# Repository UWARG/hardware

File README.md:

# Waterloo Aerial Robotics Group Hardware Repository

## Information
This repository previously held WARG electricals designs (Altium Schematics, PCBs, & Libraries) from roughly 2021 to 2022. In mid 2022 we switched solely toward Altium 365, https://warg.365.altium.com/ , and have largely abandonned this repository. Ideally we would upload completed projects to this Github for safe keeping in case anything happens with our Altium 365. 
For further documentation see Confluence, https://uwarg-docs.atlassian.net/wiki/spaces/EL/overview , or our team Discord.

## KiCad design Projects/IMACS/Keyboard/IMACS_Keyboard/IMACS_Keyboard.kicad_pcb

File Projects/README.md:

# Water System Controller

Confluence Information: https://uwarg-docs.atlassian.net/wiki/spaces/EL/pages/2765914176/Water+System+Controller

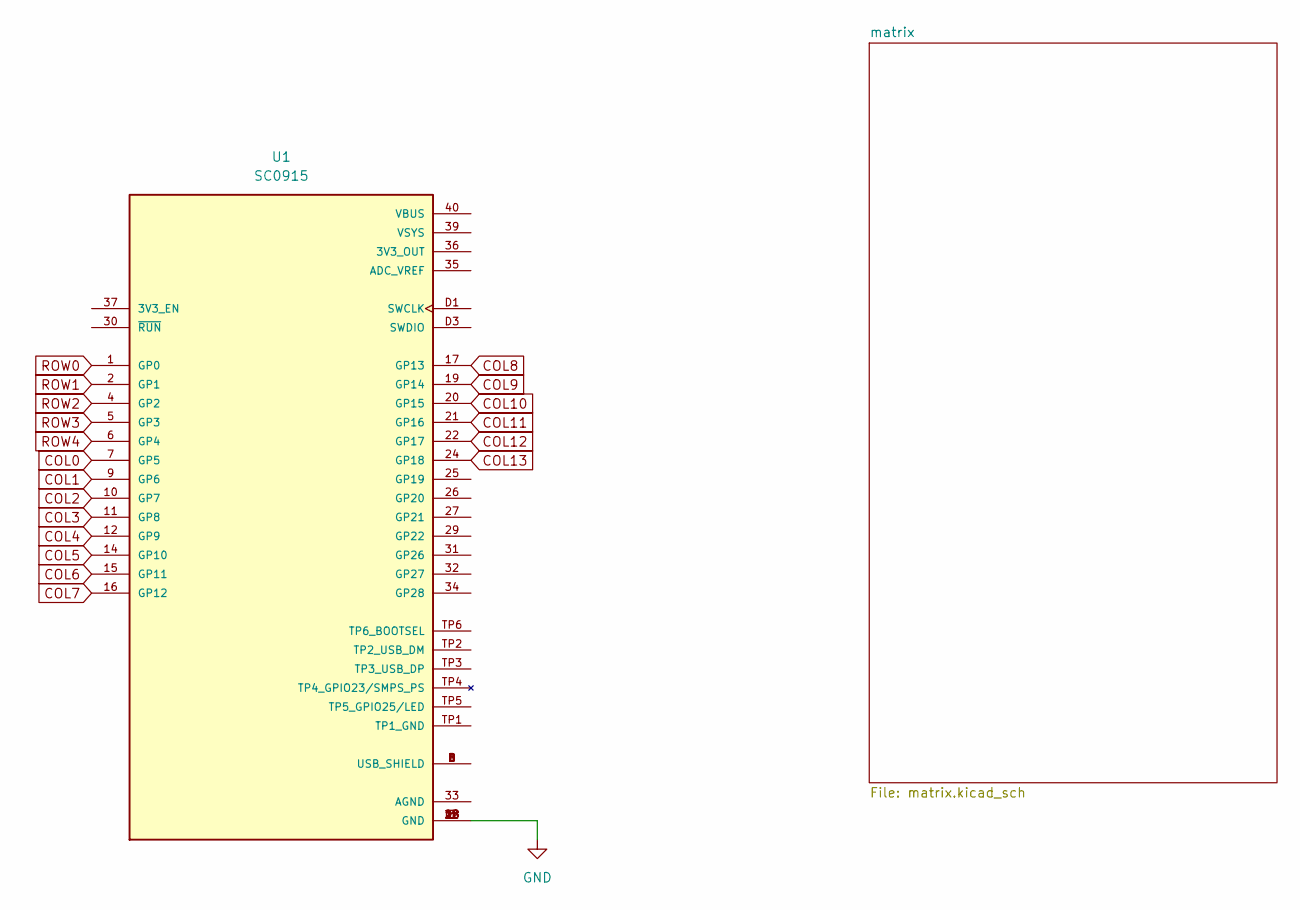
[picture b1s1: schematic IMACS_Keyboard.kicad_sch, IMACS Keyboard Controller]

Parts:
U1: SC0915; MODULE_SC0915; PARTREV 1.9

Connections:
COL0: U1.7 (GP5); also elsewhere on the board
COL1: U1.9 (GP6); also elsewhere on the board
COL2: U1.10 (GP7); also elsewhere on the board
COL3: U1.11 (GP8); also elsewhere on the board
COL4: U1.12 (GP9); also elsewhere on the board
COL5: U1.14 (GP10); also elsewhere on the board
COL6: U1.15 (GP11); also elsewhere on the board
COL7: U1.16 (GP12); also elsewhere on the board
COL8: U1.17 (GP13); also elsewhere on the board
COL9: U1.19 (GP14); also elsewhere on the board
COL10: U1.20 (GP15); also elsewhere on the board
COL11: U1.21 (GP16); also elsewhere on the board
COL12: U1.22 (GP17); also elsewhere on the board
COL13: U1.24 (GP18); also elsewhere on the board
GND: U1.3 (GND), U1.8 (GND), U1.13 (GND), U1.18 (GND), U1.23 (GND), U1.28 (GND), U1.38 (GND), U1.D2 (GND)
unnamed: U1.A (USB_SHIELD), U1.B (USB_SHIELD), U1.C (USB_SHIELD), U1.D (USB_SHIELD)
ROW0: U1.1 (GP0); also elsewhere on the board
ROW1: U1.2 (GP1); also elsewhere on the board
ROW2: U1.4 (GP2); also elsewhere on the board
ROW3: U1.5 (GP3); also elsewhere on the board
ROW4: U1.6 (GP4); also elsewhere on the board

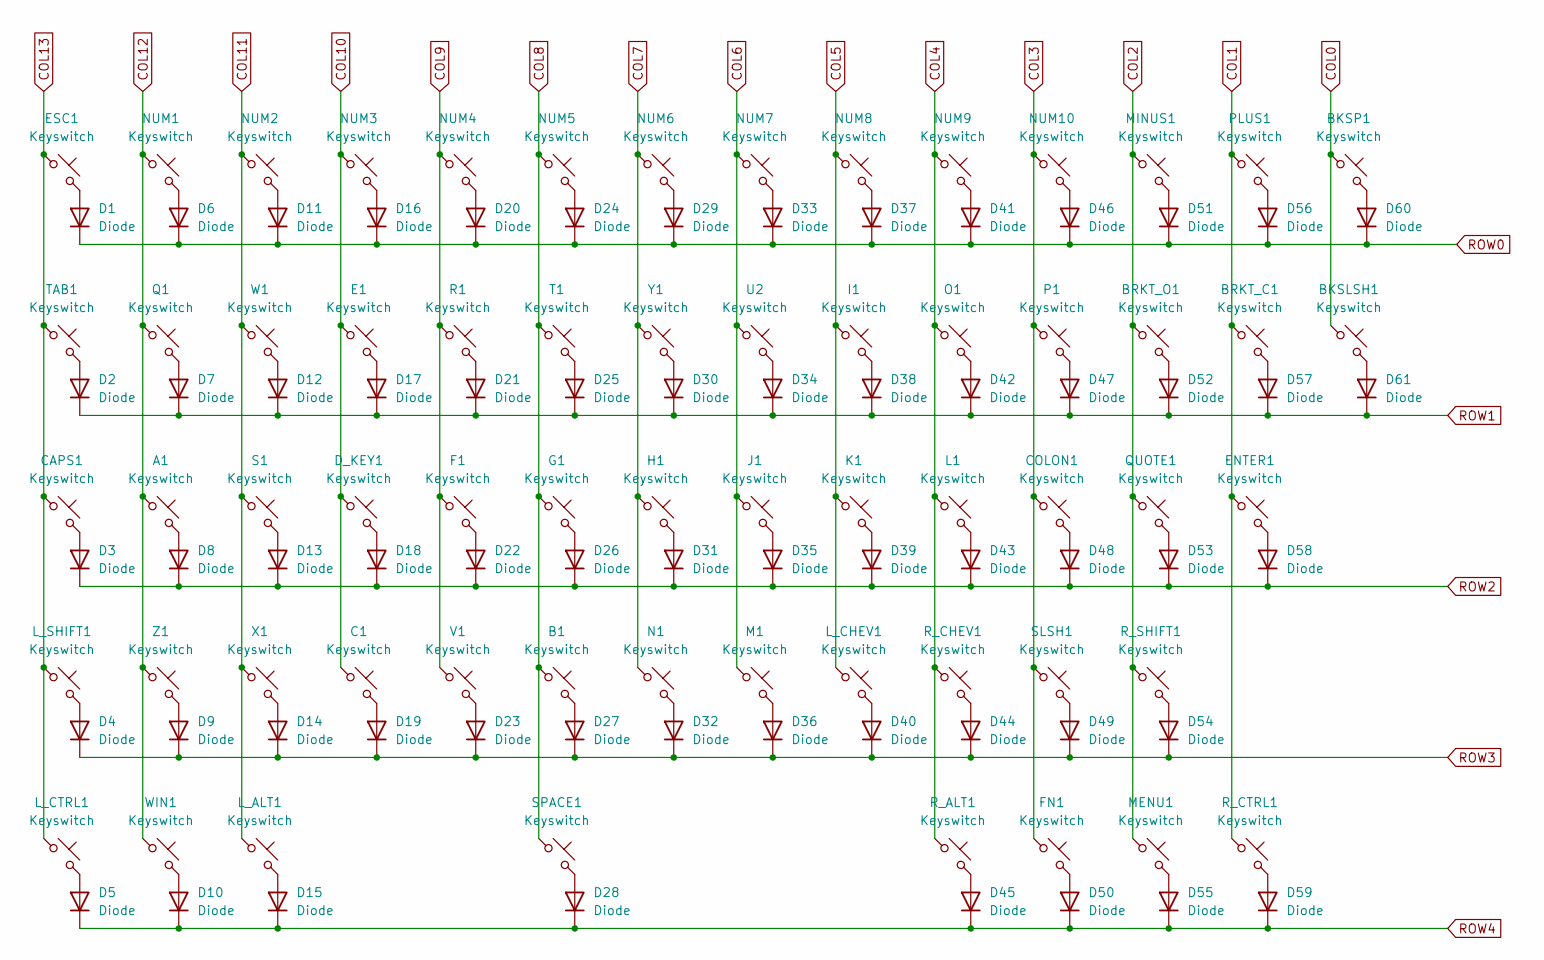
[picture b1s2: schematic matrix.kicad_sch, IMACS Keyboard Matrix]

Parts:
A1: Keyswitch; MX_PCB_1.00u
B1: Keyswitch; MX_PCB_1.00u
BKSLSH1: Keyswitch; MX_PCB_1.00u
BKSP1: Keyswitch; MX_PCB_1.00u
BRKT_C1: Keyswitch; MX_PCB_1.00u
BRKT_O1: Keyswitch; MX_PCB_1.00u
C1: Keyswitch; MX_PCB_1.00u
CAPS1: Keyswitch; MX_PCB_1.00u
COLON1: Keyswitch; MX_PCB_1.00u
D1, D2, D3, D4, D5, D6, D7, D8, D9, D10, D11, D12, D13, D14, D15, D16, D17, D18, D19, D20, D21, D22, D23, D24, D25, D26, D27, D28, D29, D30, D31, D32, D33, D34, D35, D36, D37, D38, D39, D40, D41, D42, D43, D44, D45, D46, D47, D48, D49, D50, D51, D52, D53, D54, D55, D56, D57, D58, D59, D60, D61: Diode; Diode_DO-35
D_KEY1: Keyswitch; MX_PCB_1.00u
E1: Keyswitch; MX_PCB_1.00u
ENTER1: Keyswitch; MX_PCB_1.00u
ESC1: Keyswitch; MX_PCB_1.00u
F1: Keyswitch; MX_PCB_1.00u
FN1: Keyswitch; MX_PCB_1.00u
G1: Keyswitch; MX_PCB_1.00u
H1: Keyswitch; MX_PCB_1.00u
I1: Keyswitch; MX_PCB_1.00u
J1: Keyswitch; MX_PCB_1.00u
K1: Keyswitch; MX_PCB_1.00u
L1: Keyswitch; MX_PCB_1.00u
L_ALT1: Keyswitch; MX_PCB_1.00u
L_CHEV1: Keyswitch; MX_PCB_1.00u
L_CTRL1: Keyswitch; MX_PCB_1.00u
L_SHIFT1: Keyswitch; MX_PCB_1.00u
M1: Keyswitch; MX_PCB_1.00u
MENU1: Keyswitch; MX_PCB_1.00u
MINUS1: Keyswitch; MX_PCB_1.00u
N1: Keyswitch; MX_PCB_1.00u
NUM1, NUM2, NUM3, NUM4, NUM5, NUM6, NUM7, NUM8, NUM9, NUM10: Keyswitch; MX_PCB_1.00u
O1: Keyswitch; MX_PCB_1.00u
P1: Keyswitch; MX_PCB_1.00u
PLUS1: Keyswitch; MX_PCB_1.00u
Q1: Keyswitch; MX_PCB_1.00u
QUOTE1: Keyswitch; MX_PCB_1.00u
R1: Keyswitch; MX_PCB_1.00u
R_ALT1: Keyswitch; MX_PCB_1.00u
R_CHEV1: Keyswitch; MX_PCB_1.00u
R_CTRL1: Keyswitch; MX_PCB_1.00u
R_SHIFT1: Keyswitch; MX_PCB_1.00u
S1: Keyswitch; MX_PCB_1.00u
SLSH1: Keyswitch; MX_PCB_1.00u
SPACE1: Keyswitch; MX_PCB_1.00u
T1: Keyswitch; MX_PCB_1.00u
TAB1: Keyswitch; MX_PCB_1.00u
U2: Keyswitch; MX_PCB_1.00u
V1: Keyswitch; MX_PCB_1.00u
W1: Keyswitch; MX_PCB_1.00u
WIN1: Keyswitch; MX_PCB_1.00u
X1: Keyswitch; MX_PCB_1.00u
Y1: Keyswitch; MX_PCB_1.00u
Z1: Keyswitch; MX_PCB_1.00u

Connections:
COL0: BKSLSH1.1, BKSP1.1; also elsewhere on the board
COL1: BRKT_C1.1, ENTER1.1, PLUS1.1, R_CTRL1.1; also elsewhere on the board
COL2: BRKT_O1.1, MENU1.1, MINUS1.1, QUOTE1.1, R_SHIFT1.1; also elsewhere on the board
COL3: COLON1.1, FN1.1, NUM10.1, P1.1, SLSH1.1; also elsewhere on the board
COL4: L1.1, NUM9.1, O1.1, R_ALT1.1, R_CHEV1.1; also elsewhere on the board
COL5: I1.1, K1.1, L_CHEV1.1, NUM8.1; also elsewhere on the board
COL6: J1.1, M1.1, NUM7.1, U2.1; also elsewhere on the board
COL7: H1.1, N1.1, NUM6.1, Y1.1; also elsewhere on the board
COL8: B1.1, G1.1, NUM5.1, SPACE1.1, T1.1; also elsewhere on the board
COL9: F1.1, NUM4.1, R1.1, V1.1; also elsewhere on the board
COL10: C1.1, D_KEY1.1, E1.1, NUM3.1; also elsewhere on the board
COL11: L_ALT1.1, NUM2.1, S1.1, W1.1, X1.1; also elsewhere on the board
COL12: A1.1, NUM1.1, Q1.1, WIN1.1, Z1.1; also elsewhere on the board
COL13: CAPS1.1, ESC1.1, L_CTRL1.1, L_SHIFT1.1, TAB1.1; also elsewhere on the board
unnamed: D1.2 (A), ESC1.2
unnamed: D2.2 (A), TAB1.2
unnamed: CAPS1.2, D3.2 (A)
unnamed: D4.2 (A), L_SHIFT1.2
unnamed: D5.2 (A), L_CTRL1.2
unnamed: D6.2 (A), NUM1.2
unnamed: D7.2 (A), Q1.2
unnamed: A1.2, D8.2 (A)
unnamed: D9.2 (A), Z1.2
unnamed: D10.2 (A), WIN1.2
unnamed: D11.2 (A), NUM2.2
unnamed: D12.2 (A), W1.2
unnamed: D13.2 (A), S1.2
unnamed: D14.2 (A), X1.2
unnamed: D15.2 (A), L_ALT1.2
unnamed: D16.2 (A), NUM3.2
unnamed: D17.2 (A), E1.2
unnamed: D18.2 (A), D_KEY1.2
unnamed: C1.2, D19.2 (A)
unnamed: D20.2 (A), NUM4.2
unnamed: D21.2 (A), R1.2
unnamed: D22.2 (A), F1.2
unnamed: D23.2 (A), V1.2
unnamed: D24.2 (A), NUM5.2
unnamed: D25.2 (A), T1.2
unnamed: D26.2 (A), G1.2
unnamed: B1.2, D27.2 (A)
unnamed: D28.2 (A), SPACE1.2
unnamed: D29.2 (A), NUM6.2
unnamed: D30.2 (A), Y1.2
unnamed: D31.2 (A), H1.2
unnamed: D32.2 (A), N1.2
unnamed: D33.2 (A), NUM7.2
unnamed: D34.2 (A), U2.2
unnamed: D35.2 (A), J1.2
unnamed: D36.2 (A), M1.2
unnamed: D37.2 (A), NUM8.2
unnamed: D38.2 (A), I1.2
unnamed: D39.2 (A), K1.2
unnamed: D40.2 (A), L_CHEV1.2
unnamed: D41.2 (A), NUM9.2
unnamed: D42.2 (A), O1.2
unnamed: D43.2 (A), L1.2
unnamed: D44.2 (A), R_CHEV1.2
unnamed: D45.2 (A), R_ALT1.2
unnamed: D46.2 (A), NUM10.2
unnamed: D47.2 (A), P1.2
unnamed: COLON1.2, D48.2 (A)
unnamed: D49.2 (A), SLSH1.2
unnamed: D50.2 (A), FN1.2
unnamed: D51.2 (A), MINUS1.2
unnamed: BRKT_O1.2, D52.2 (A)
unnamed: D53.2 (A), QUOTE1.2
unnamed: D54.2 (A), R_SHIFT1.2
unnamed: D55.2 (A), MENU1.2
unnamed: D56.2 (A), PLUS1.2
unnamed: BRKT_C1.2, D57.2 (A)
unnamed: D58.2 (A), ENTER1.2
unnamed: D59.2 (A), R_CTRL1.2
unnamed: BKSP1.2, D60.2 (A)
unnamed: BKSLSH1.2, D61.2 (A)
ROW0: D1.1 (K), D6.1 (K), D11.1 (K), D16.1 (K), D20.1 (K), D24.1 (K), D29.1 (K), D33.1 (K), D37.1 (K), D41.1 (K), D46.1 (K), D51.1 (K), D56.1 (K), D60.1 (K); also elsewhere on the board
ROW1: D2.1 (K), D7.1 (K), D12.1 (K), D17.1 (K), D21.1 (K), D25.1 (K), D30.1 (K), D34.1 (K), D38.1 (K), D42.1 (K), D47.1 (K), D52.1 (K), D57.1 (K), D61.1 (K); also elsewhere on the board
ROW2: D3.1 (K), D8.1 (K), D13.1 (K), D18.1 (K), D22.1 (K), D26.1 (K), D31.1 (K), D35.1 (K), D39.1 (K), D43.1 (K), D48.1 (K), D53.1 (K), D58.1 (K); also elsewhere on the board
ROW3: D4.1 (K), D9.1 (K), D14.1 (K), D19.1 (K), D23.1 (K), D27.1 (K), D32.1 (K), D36.1 (K), D40.1 (K), D44.1 (K), D49.1 (K), D54.1 (K); also elsewhere on the board
ROW4: D5.1 (K), D10.1 (K), D15.1 (K), D28.1 (K), D45.1 (K), D50.1 (K), D55.1 (K), D59.1 (K); also elsewhere on the board

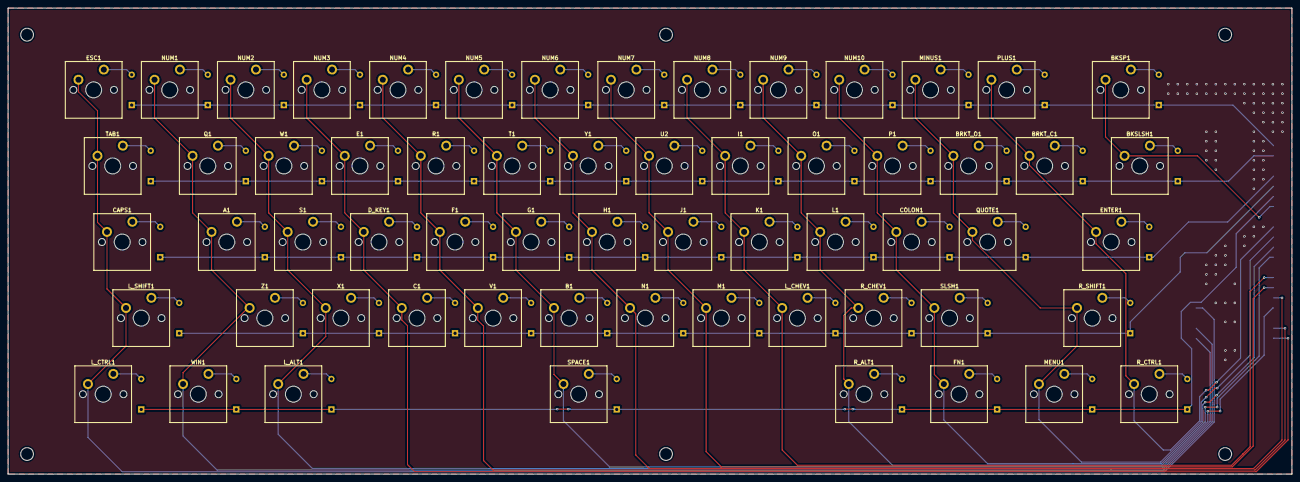
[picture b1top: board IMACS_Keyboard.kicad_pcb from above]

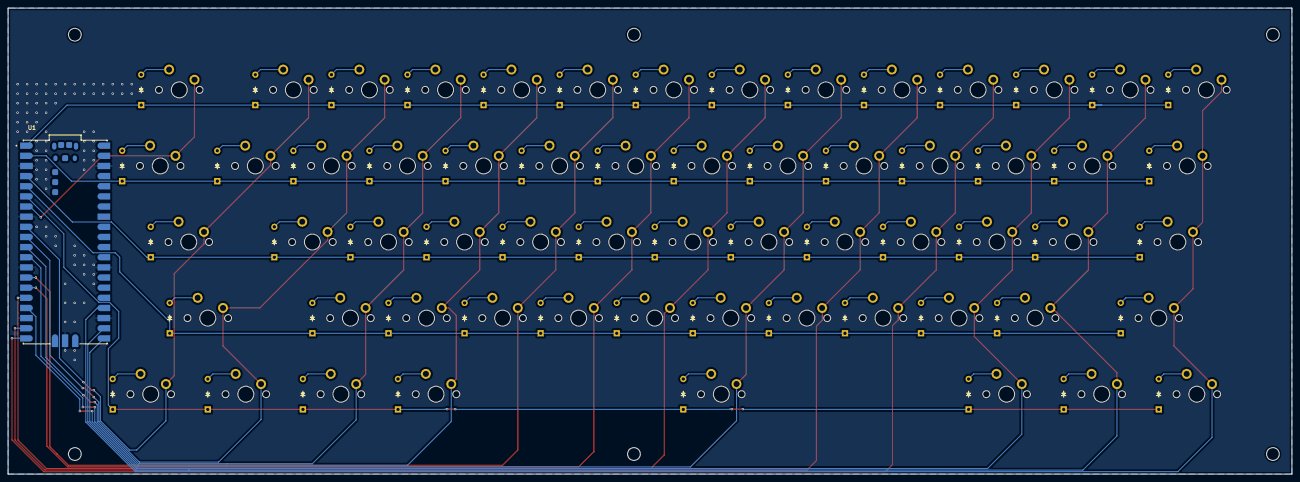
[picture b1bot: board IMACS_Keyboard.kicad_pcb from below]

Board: 2 copper layers, 321.5 x 116.7 mm, 123 parts (62 on the bottom side), 82 nets.

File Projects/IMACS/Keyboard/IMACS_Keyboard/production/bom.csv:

Designator,Footprint,Quantity,Value,LCSC Part #
"A1, B1, BKSLSH1, BKSP1, BRKT_C1, BRKT_O1, C1, CAPS1, COLON1, D_KEY1, E1, ENTER1, ESC1, F1, FN1, G1, H1, I1, J1, K1, L1, L_ALT1, L_CHEV1, L_CTRL1, L_SHIFT1, M1, MENU1, MINUS1, N1, NUM1, NUM10, NUM2, NUM3, NUM4, NUM5, NUM6, NUM7, NUM8, NUM9, O1, P1, PLUS1, Q1, QUOTE1, R1, R_ALT1, R_CHEV1, R_CTRL1, R_SHIFT1, S1, SLSH1, SPACE1, T1, TAB1, U2, V1, W1, WIN1, X1, Y1, Z1",MX_PCB_1.00u,61,Keyswitch,
"D1, D10, D11, D12, D13, D14, D15, D16, D17, D18, D19, D2, D20, D21, D22, D23, D24, D25, D26, D27, D28, D29, D3, D30, D31, D32, D33, D34, D35, D36, D37, D38, D39, D4, D40, D41, D42, D43, D44, D45, D46, D47, D48, D49, D5, D50, D51, D52, D53, D54, D55, D56, D57, D58, D59, D6, D60, D61, D7, D8, D9",Diode_DO-35,61,Diode,
U1,MODULE_SC0915,1,SC0915,

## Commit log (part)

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2021-10-29 ZEROPILOT2.0: Changed styling preferences slightly and reorganized sheets
2021-10-29 GIMBAL: Renamed power ports and updated notes
2021-10-31 FWSHIELD: Added bypass cap
2021-11-01 GIMBAL: Included 0 ohm resistors for servo power selection
2021-11-03 ZEROPLIOT2: Added PDF
2021-11-05 ZEROPILOT2: add bypass caps for FTDI USB chip and LIBRARIES: updated FTDI chip symbol
2021-11-05 Created JLCPCB Design Rules and Stackups
2021-11-05 ZEROPILOT2.0 AND LIBRARIES: Updated several component links to schematic sheets and added a few pin 1 indicators to connector PCB footprints
2021-11-06 LIBRARIES and ZEROPILOT2.0: use passive pins for H7 and F0
2021-11-06 GIMBAL & LIBRARIES: Redid PCB placement and adjusted screw terminal footprint
2021-11-07 ZEROPILOT2: Removed F0 & H7 LSE
    -As directed by Sahil
    -F0 and H7 HSEs still need to be replaced with in stock alternatives
2021-11-07 FWTRAINING: Adding the servo connectors (Input & Output)
2021-11-08 GIMBAL: Adjusted 0 ohm resistor placement
2021-11-08 ZEROPILOT2.0: add FW request - USART3 breakout VectorNAV GPS Failure
2021-11-08 ZEROPILOT2.0: WIP F0 SPI and I2C
2021-11-08 FWTRAINNING: Minor Styling Changes
    -Resolved 50mil grid issues
    -Added engineer name
    -Renamed power net to 5V
    -Added note for decoupling capacitor
    -Reordered component placement
2021-11-09 Revert "ZEROPILOT2: Removed Interchip SPI NSS"
    This reverts commit 1d9dee945d0cea79a489fabb505752ab9059d955.
2021-11-09 ZEROPILOT2 & LIBRARIES: Resourced Blue LED, previous one was out of stock
2021-11-09 POWER DISTRIBUTION: Recreated project files
2021-11-09 ZEROPILOT2: Updated schematic pdf
2021-11-10 LIBRARIES: Fixed 1uF 50V Murata MLCC capacitor Design Item ID
2021-11-11 FWTRAINING: Fixing headers, power nets, and decoupling caps
    - Added 2 1uf caps to VREF and VDD
    - Added pot circuit
    - Removed 2 servo connectors
    - Changed pinout of 1x3 input connector
    - Switched to 3V3 power net
    - Updated LED resistor to match with 3V3 power net
2021-11-12 LIBRARIES: Footprint Improvements
    -Reoriented STM32H7 3D body
    -Resized XTAL-OSC-XO-CMOS pin one dot
    -Updated USB_CONN_292303-1 comment
    -Fixed CONN4_292303-1 footprint, removed garbage from layers, expanded silk screen
    -Cleaned up MOLEX_104031-0811 footprint silk screen
    -Cleaned up MCP9701T footprint & silk screen
2021-11-13 FWTRAINING: Styling and layout changes
    - Replaced unused ADC channels with no ERC
    - Added placement note to decoupling caps
    - Rotated pot 90deg
    - Fixed misaligned pot designator
    - Moved connection headers to left side of schematic
    - Switched pot and LED position
2021-11-13 LIBRARIES: updated assorted footprints
2021-11-13 LIBRARIES & ZEROPILOT2: Sourced new MOSFET
2021-11-13 LIBRARIES: Updated components to be in stock
    -Updated ferrite bead in sheets
    -Updated 6x1 header to in stock alternative
    -Updated 0ohm
2021-11-13 FWTRAINING: Styling changes and updated pin order for MCP
2021-11-13 GIMBAL: Added board outline on keepout layer and added board measurements
2021-11-13 ZEROPILOT: Updated schematic sheets
    -Updated blue LED
2021-11-17 ZEROPILOT2.0: Updated some placements
2021-11-18 POWERDISTRIBUTION and LIBRARIES: Fixing pin layout of LM25116 buck IC and added VCC and BOOTSTRAP capacitors
2021-11-18 POWER DISTRIBUTION and LIBRARIES: Minor styling changes and PDF export
2021-11-19 FW TRAINING: Adjusted styling preferences
2021-11-19 ZEROPILOT2: Added forgotten I2C pullup resistors.
    -Did not re-annotate and updated PCB
2021-11-20 ZEROPILOT2.0: moved H7 bypass caps nearby respective pins, other various updates
2021-11-20 LIBRARIES: Re-Sourced pot and added 3d model.
2021-11-20 ZEROPILOT2: Finished Initial Placement
    -All components are on the PCB and close to their final location
2021-11-21 ZEROPILOT2.0: add 4 layers board stackup, minor adjustments and other various updates
2021-11-21 FWTRAINING: First pass at routing
2021-11-22 ZEROPILOT2: More Placement Progress
2021-11-22 ZEROPILOT2: Fixed some silk to solder mask design errors
2021-11-24 FWTRAINING: Removing GND vias and tracks & slight variation on cap routing
2021-11-24 POWER DISTRIBUTION and LIBRARIES: Added footprints for switching diode and started PCB component placement
2021-11-25 POWER DISTRIBUTION and LIBRARIES: Added enable switch and multiple schematic sheets for organization
2021-11-26 GIMBAL: Completed PCB layout and generated output files for manufacturing
2021-11-27 FW TRAINING: Finished PCB Layout and exported output files for manufacturing
2021-11-27 FW Training: Updated FW Training Shield project with DRC template file
2021-11-28 ZEROPILOT2.0: 2nd attempt at placement (more spaced out, emphasis on space for routing etc.)
2021-11-29 LIBRARIES: add BQ76925 and MSP430 MCU
2021-12-01 ZEROPILOT2.0: add TP for extra I2C, SPI and UART
2021-12-02 ZEROPILOT2.0: Modified input power and microSD circuitry placement
2021-12-02 ZEROPILOT2.0: Modified decoupling capacitor placement on H7 chip
2021-12-04 ZEROPILOT: Corrected PWM header pins
2021-12-05 ZEROPILOT: Assorted labelling of Zeropilot connector
2021-12-23 ZEROPILOT2: Added Mounting Holes
    - Placed Mounting Hole in preliminary locations
2021-12-25 ZEROPILOT2: Added Graphics
2021-12-28 POWER DISTRIBUTION: Completed layout and added 3 2-pin headers for 5V outputs
2021-12-28 ZEROPILOT2: Refined routing on J21
2021-12-29 POWER DISTRIBUTION: Fixed AGND plane
2021-12-30 POWER DISTRIBUTION: Fixed via stitching
2021-12-31 ZEROPILOT2: Minor adjustments
2022-01-01 POWER DISTRIBUTION: Changed thermal relief for 5V decoupling capacitors
2022-01-05 ZEROPILOT2: Updated .step & .pdf
2022-01-05 LIBRARIES: add BQ76930 and footprint
2022-01-13 BMS: Cleaned up some circuitry around the IC
2022-01-15 BMS: removed unecessary components
2022-01-16 BMS: Fixed up circuitry around BQ78350 and LIBRARIES: Added 5.6 Zener diode
2022-01-25 finished polygons - just need to swap the DRV8353 footprint with one I modified
2022-01-27 BMS: Added NCH FETs and LIBRARIES: Added CSD17522Q5A and BSS138K-13 FETS
2022-01-29 BMS: Added boot circuit and LIBRARIES: Added 3.01k resistor
2022-02-02 BMS: Added temp sensing circuit and LIBRARIES: Added 10k thermistor
2022-02-10 BMS: Added BOOT LED and LIBRARIES: Added 3k resistor
2022-02-12 Finished making Joe's chaings. Ready for a second review!
2022-02-13 BMS: Updated BMS schematic
2022-02-13 BMS: Ready for review, output PDF created
2022-02-14 BMS: Changed to hierarchical structure
2022-02-16 BMS: Began PCB component placement
2022-02-16 BMS: Pushed state info changes in prjpcb file
2022-02-18 BMS: Completed PCB placement
2022-03-01 POWER DISTRIBUTION - ETHAN: Common components on schematic placed
2022-03-03 POWER DISTRIBUTION - ETHAN: Added new components to library for my design
2022-03-05 POWER DISTRIBUTION - ETHAN: Finished initial draft of schematic
2022-03-06 fixing footprint connections and making changes to motor controller power input pads
2022-03-06 POWER DISTRIBUTION - ETHAN: Add 6.8uH inductor
2022-03-07 ADMIN: Modified PDB folder structure
2022-03-08 LIBRARIES: Added silkscreen outlines to all resistors/capacitor footprints and components strictly for PDB
2022-03-08 POWER DISTRIBUTION: Completed initial PCB placement
2022-03-09 POWER DISTRIBUTION - ETHAN: Initial component placement
2022-03-09 POWER DISTRIBUTION: Continued PCB layout. Almost complete
2022-03-10 LIBRARIES: Added castellated pin (2mm hole size, 3mm diameter)
2022-03-10 POWER DISTRIBUTION: Completed PCB layout
2022-03-12 LIBRARIES: Add 10m ohm 1206 resistor
2022-03-12 LIBARIRES: Modified castellated pin
2022-03-13 POWER DISTRIBUTION - ETHAN: Polygons created
2022-03-14 POWER DISTRIBUTION - ETHAN: Fix vias
2022-03-17 POWER DISTRIBUTION - ETHAN: Add 10uF X7R cap
2022-03-18 LIBRARIES: Create pcb component for buck converter
2022-03-20 BMS: Added routing for top/bottom signal layers
2022-03-22 POWER DISTRIBUTION and LIBRARIES: Modified design to 250kHz
2022-03-22 Updated Schematic Sheets
2022-03-22 Removed Clone of Nav Lights Folder
2022-03-23 Updated Gerber
2022-03-23 Generated BOM File
2022-03-23 LIBRARIES: Added CSS2H-3920R-L200F
2022-03-24 Revised Board with Daniel
    Added 4 ground vias, next steps: fix component placement, remove wires, use polygons and make board neater
2022-03-24 Poured polygons for resistors, tidied up component spacing
    Ensured all components are spaced 2cm apart, poured polygons over all resistors
2022-03-24 Nav Lights Design Changes (Listed in Description)
    Changed Schematic symbol design (Power Pad and GND pad). Aligned Vias, lowered impedance by routing polygon pours, resized and fixed resistor footprint to match dimensions.
2022-03-24 Fixed polygon net antennae errors and polygon errors by re-ordering polygon pour order
2022-03-24 Enlarged GND Tracks, reduced size of vias, fixed polygon pour issue which should lower impedance
2022-03-24 BMS: Finished routing for VCC and GND
2022-03-25 Aligned GND vias
2022-03-25 Re-generated Schematic, BOM and Gerber Files for the updated model
2022-03-25 NAVLIGHTS: Fixed Resistor Polygon Pours to avoid impedance, re-generated Gerber Files
2022-03-26 NAVLIGHTS: Fixed small polygons to be direct connect, and large polygons (5V and GND) have thermal relief. Removed Thermal Relief on Resistors.
2022-03-28 NAVLIGHTS: Edited LED Supplier Links, Footprint. Updated 3D PCB Model
2022-03-28 NAVLIGHTS: Added additional calculations
    NAVLIGHTS: Added additional calculations for Green LED and corresponding resistor
2022-03-28 NAVLIGHTS: Fixed LED Footprint
    Changed Anode and Cathode
2022-03-29 NAVLIGHTS: Design Changes V2
    Moved pads a bit farther apart, rotated silkscreen sideways, centered them above the pads, changed top layer polygon to GND and connected 5V to 5V pads on the resistors by simply using a thick trace 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
2022-03-29 BMS: Completed polygon pouring
2022-03-31 BMS: started via stitching
2022-03-31 BMS: Updated via stitching
2022-04-02 BMS: Updated routing, added silkscreen heading
2022-04-06 POWER DISTRIBUTION - ETHAN: Component clean-up
2022-04-10 BMS: Fixed via stitching in some areas
2022-04-10 BMS: Fixed silkscreens
2022-04-13 POWER DISTRIBUTION - ETHAN: Begin panelization of PDB
2022-04-16 POWER DISTRIBUTION - ETHAN: Redo board cutouts, add mounting holes and fiducials
2022-05-11 POWER DISTRIBUTION - ETHAN: Add BomDoc
2022-05-21 BOOTCAMP: Added WARG EE Bootcamp files
2022-06-18 BOOTCAMP: Modified battery protection, current sense, buck converter, voltage sense circuits
2022-06-21 BOOTCAMP: Modified schematic
2022-06-21 BOOTCAMP: Cleaned up file structure
2023-02-15 Added layers file
2023-03-05 Formatting Fix
2023-03-05 Added context READMEs
2024-01-13 Fixed common value detection algorithm & updated comment
2024-01-15 updated ZP3 interface design files
2024-01-15 initial commit for 12V-5V buck design files
2024-04-14 Added KiCad Arduino Tracking Antenna PCB
2024-06-25 Create 12-5V @ 5A Protected Buck
2024-06-25 added README.md
2024-08-12 Add IMACS panel-mount mechanical keyboard PCB (#2)
    * Initial project commit
    Modified version from initial production run. Removed logic level shifter and added diode to reduce voltage to LED. Removed 3D_FIX connection from GPS to Arduino. Improved Arduino grounding.
    * Added IMACS keyboard
2024-09-04 Added CAN Splitter Project
2024-09-04 Uploading project
2024-09-05 Minor improvements
2024-09-30 harness initial commit
2024-10-02 fixed video system schematic
2024-10-15 Actually added files
2024-10-30 Added STEP file for rpi interface rev b
2024-11-12 12-5V Buck + ELRS RX added
2024-11-13 USB-C Sink added
2024-11-15 Add files via upload
    added the correct files into a project folder
2024-11-15 Added M3 Tracking Antenna Controller Rev 2 files
2024-11-19 Add updated logo png
2024-11-20 updated rpi harness schematic
2025-02-17 Added titles & details
2025-03-09 drew all eclipse harness
2025-03-10 update motor text
2025-03-27 Added RPi Interface Rev. C PCB files
